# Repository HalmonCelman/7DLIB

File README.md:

# 7DLIB
It's a library for 7 segment 4 digits display LED with common anode
It's completely free to commercial and non-commercial use, but you must give information that this library was written by KK

platform: ATTiny2313 (default for AVR) or STM32H725VGxx(default for STM32) 
	but all code is written to work on all platforms 

see schema ( in folder schemat_i_inne ) to all information of example usage of this library

How to use?
```
1. Create project or makefile with all files from library( DLED.c, DLED.h, DLED_config.h, lldrivers.c )
2. Configure DLED_SYS in DLED_config.h↓
	select platform on which you are:
	 	0-AVR 
	 	1-STM32
	 	2,3... - another platform ↓
	 	you must write by yourself low level drivers, see file low_level.txt to more information
	 
3. Configure all connections in dled_configure.h
	 
4. You must generate interval to use dled_int(), the best option is to generate 
   interval 200 times per second to 50Hz refreshing rate (mulitplexing)

    it's all! you can now modify what is on screen with dled_set() and other functions
    ( all functions are described in functions.txt )
```
How to use example?
```
1. Connect all same as in schematic 
2. Open project with example.
( if it's not opening properly you must do point 1 and 2 in "How to use?" and join main.c )*
3. Build and run on your MCU
   See if it's working.
```

Have fun with this library ;)

```
* - sometimes this operation need change in lldrivers.c, main.c and DLED.c, because directory to the DLED.h may change
It depends on how you add files to project.
```

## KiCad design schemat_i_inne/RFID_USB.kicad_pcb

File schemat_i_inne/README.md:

In dokumentacje/ are datasheets for all of the components used in this project.

In 7DLIB_STM32 is sample schematic to this project on STM32H725VGxx

In 7DLIB_AVR is sample schematic to this project on ATtiny2313

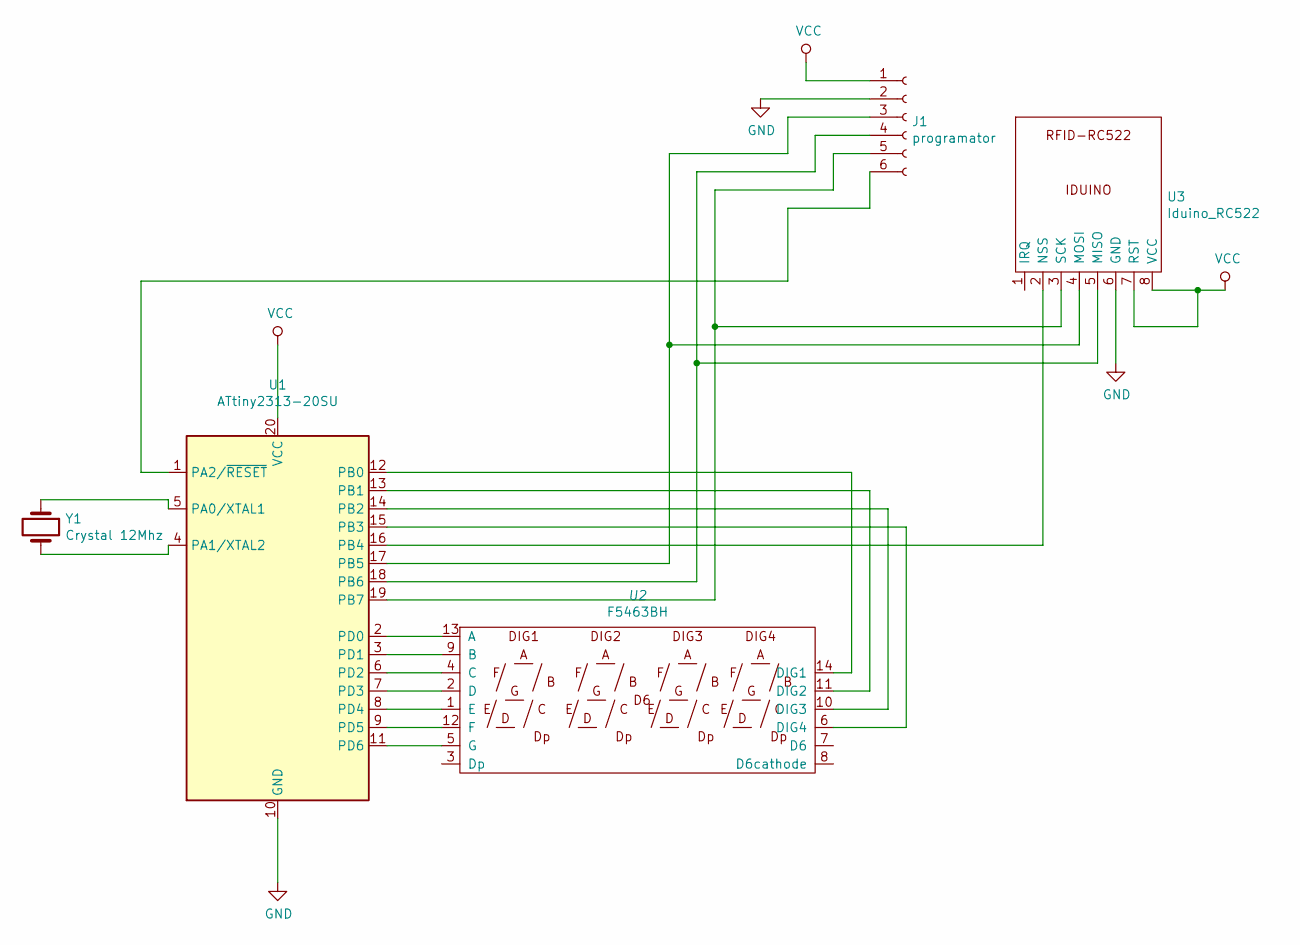
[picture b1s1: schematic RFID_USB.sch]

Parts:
J1: programator; PinSocket_1x06_P2.54mm_Vertical
U1: ATtiny2313-20SU; SOIC-20W_7.5x12.8mm_P1.27mm
U2: F5463BH
U3: Iduino_RC522; PinSocket_1x08_P2.54mm_Vertical
Y1: Crystal 12Mhz; Crystal_HC52-6mm_Vertical

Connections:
GND: J1.2, U1.10 (GND), U3.6 (GND)
unnamed: J1.3, U1.17 (PB5), U3.4 (MOSI)
unnamed: J1.4, U1.18 (PB6), U3.5 (MISO)
unnamed: J1.5, U1.19 (PB7), U3.3 (SCK)
unnamed: J1.6, U1.1 (PA2/~RESET)
unnamed: U1.2 (PD0), U2.13 (A)
unnamed: U1.3 (PD1), U2.9 (B)
unnamed: U1.4 (PA1/XTAL2), Y1.2
unnamed: U1.5 (PA0/XTAL1), Y1.1
unnamed: U1.6 (PD2), U2.4 (C)
unnamed: U1.7 (PD3), U2.2 (D)
unnamed: U1.8 (PD4), U2.1 (E)
unnamed: U1.9 (PD5), U2.12 (F)
unnamed: U1.11 (PD6), U2.5 (G)
unnamed: U1.12 (PB0), U2.14 (DIG1)
unnamed: U1.13 (PB1), U2.11 (DIG2)
unnamed: U1.14 (PB2), U2.10 (DIG3)
unnamed: U1.15 (PB3), U2.6 (DIG4)
unnamed: U1.16 (PB4), U3.2 (NSS)

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
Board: 2 copper layers, 5 parts (0 on the bottom side), 20 nets, no tracks yet.

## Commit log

2022-03-28 Library v1.0.5
    some minor bugs fixed
2022-03-28 My project
2022-04-11 README, schemat i dokumentacje
    zaktualizowano README, dodano i uporzadkowano schematy
    dodano dokumentacje STM32H725VGxx
2022-04-11 README fix
    some README fix
2022-04-11 README once again
2022-04-11 README change
2022-04-11 test README
2022-04-11 README working
2022-04-14 Uzupelniona instrukcja
    uzupelniono instrukcje i zmieniono troche strukture plikow
2022-04-14 Zmiana schematu
    zmieniono schemat dla stm32
2022-04-14 Naprawione kolory
    Naprawione kolory i schemat pdf dla AVR
2022-04-14 Mniejsze poprawki
    mało istotne poprawki kosmetyczne
2022-04-17 STM32 projekt dodany
    Dodano szkic projektu STM32 i trochę zmieniono bibliotekę
    aby była bardziej uniwersalna, oraz pare innych malych zmian
2022-04-17 usuniecie niepotrzebnych plikow
2022-09-21 README corrected
2023-12-05 LICENSE Added
